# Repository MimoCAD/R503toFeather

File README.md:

# Pinout

## Adafruit Feather RP2350 HSTX

## Grow R503 Pro

## Connections
| # | R503 Pro Wire Color                    | Name   | PIN # | Pin Name               | Notes                            |
| - |                 :---:                  | :---:  | :---: |          :---:         |               :---:              |
| 1 | $${\color{red}RED \space Wire}$$       | Power  |   3V3 | $${\color{red}3V3}$$   | 3.3 Volts (Top Left Of Feather). |
| 2 | $${\color{black}BLACK \space Wire}$$   | GND    |   GRD | $${\color{black}GND}$$ | Ground (Right Under 3.3 Pins).   |
| 3 | $${\color{yellow}YELLOW \space Wire}$$ | TXD    |    01 | $${\color{green}RX}$$  | TX on R503 <> RX on the Feather. |
| 4 | $${\color{green}GREEN \space Wire}$$   | RXD    |    00 | $${\color{yellow}TX}$$ | RX on R503 <> TX on the Feather. |
| 5 | $${\color{blue}BLUE \space Wire}$$     | Wakeup |    02 | $${\color{BLUE}SDA}$$  | Finger Detection (Pulled High).  |
| 6 | $${\color{white}WHITE \space Wire}$$   | Touch  |   3V3 | $${\color{red}3V3}$$   | 3.3 Volts (Top Left Of Feather). |

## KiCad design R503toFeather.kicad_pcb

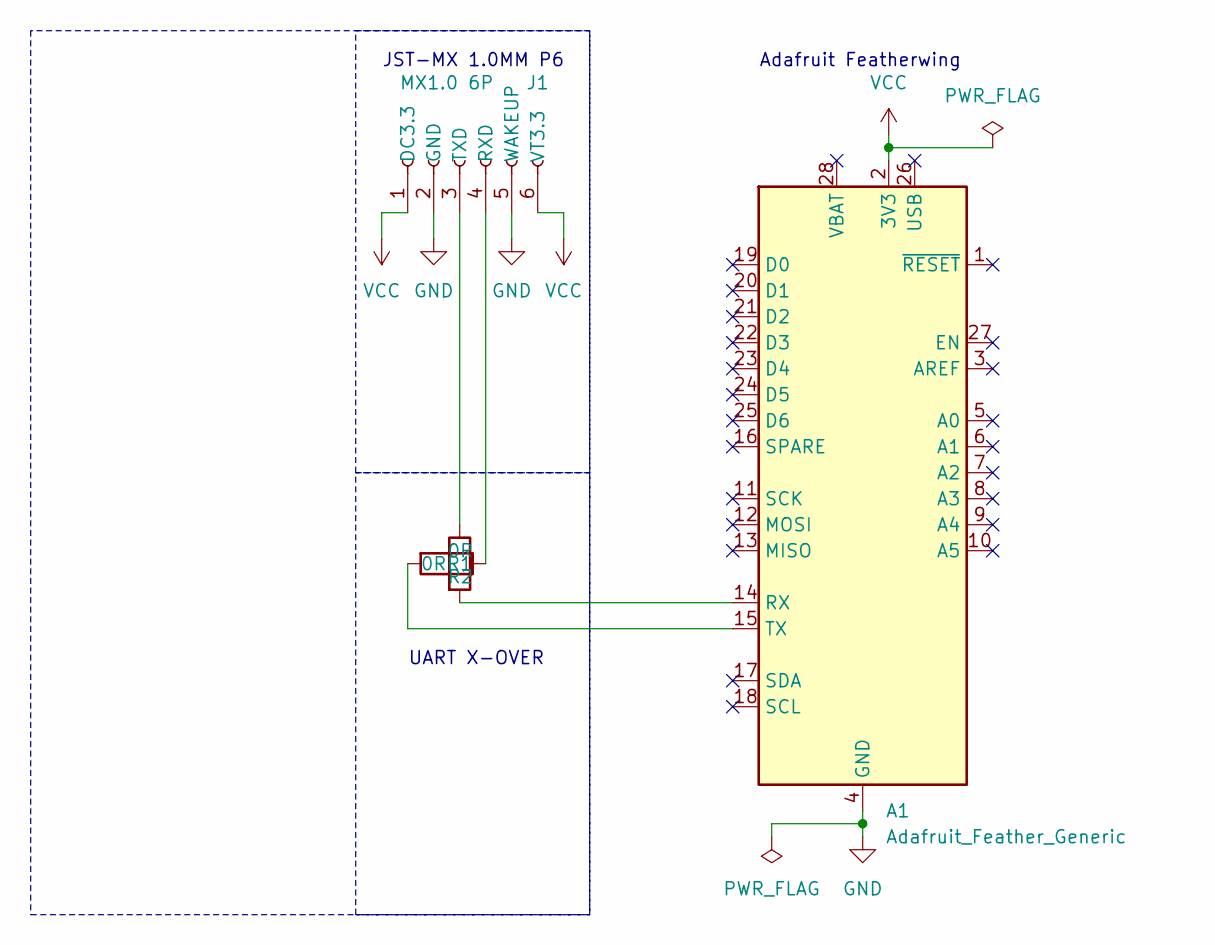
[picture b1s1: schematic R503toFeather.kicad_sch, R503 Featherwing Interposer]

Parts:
A1: Adafruit_Feather_Generic; Adafruit_Feather
J1: MX1.0 6P; JST_SHL_SM06B-SHLS-TF_1x06-1MP_P1.00mm_Horizontal
R1, R2: 0R; R_1206_3216Metric

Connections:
GND: A1.4 (GND), J1.2 (GND), J1.5 (WAKEUP)
unnamed: A1.14 (RX), R2.2
unnamed: A1.15 (TX), R1.2
unnamed: J1.4 (RXD), R1.1
unnamed: J1.3 (TXD), R2.1
VCC: A1.2 (3V3), J1.1 (DC3.3), J1.6 (VT3.3)

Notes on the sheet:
UART X-OVER
JST-MX 1.0MM P6
Adafruit Featherwing

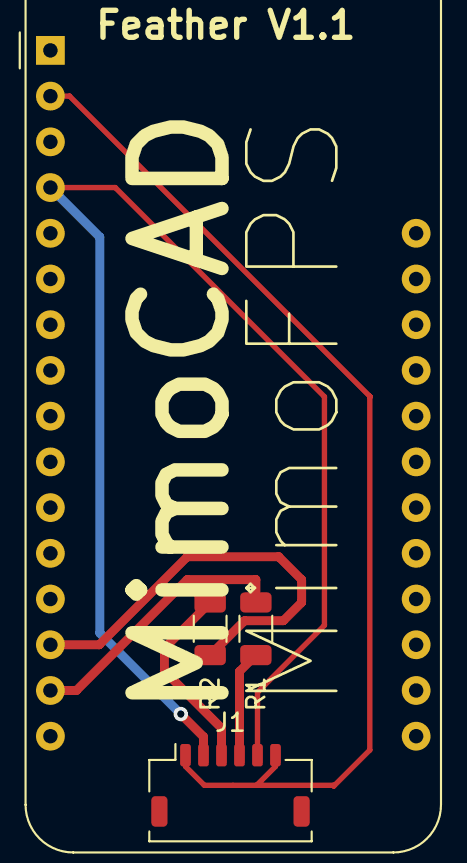
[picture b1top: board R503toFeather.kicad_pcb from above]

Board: 2 copper layers, 4 parts (0 on the bottom side), 6 nets.

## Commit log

2024-08-15 Hopefully Functional.
2025-05-18 RP2350 HSTX Production Version
2025-05-18 Update README.md
    Update for Adafruit Feather RP2350 HSTX
2026-03-16 Fixed J1's 2 Pin. Corrected to GND.

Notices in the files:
R503toFeather.kicad_sch:
creativecommons.org/licenses/by/4.0
License: CC BY 4.0
